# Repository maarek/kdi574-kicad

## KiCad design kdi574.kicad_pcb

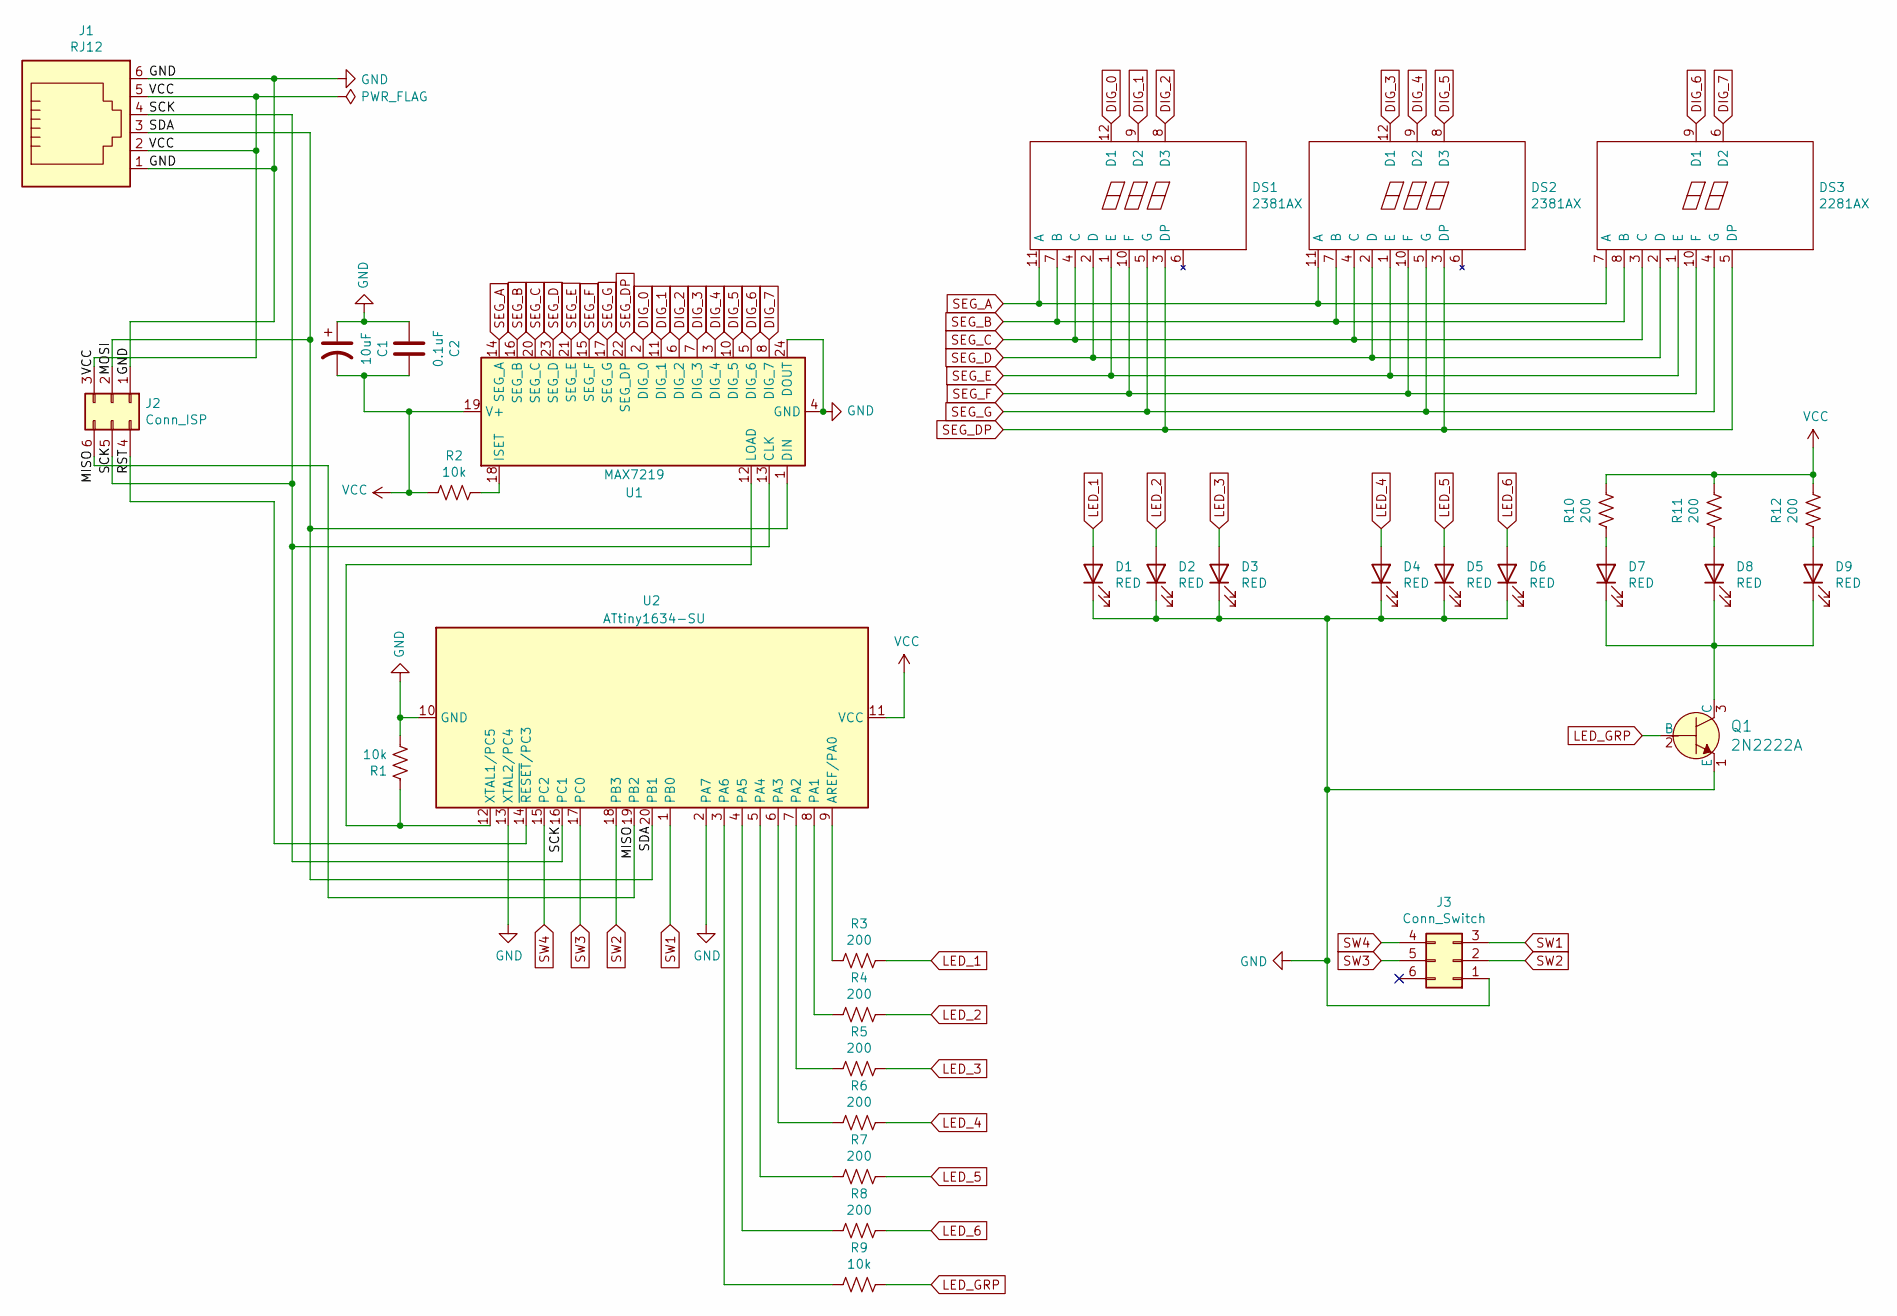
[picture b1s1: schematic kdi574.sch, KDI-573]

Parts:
C1: 10uF; C_1206_3216Metric
C2: 0.1uF; C_1206_3216Metric
D1, D2, D3, D4, D5, D6, D7, D8, D9: RED; LED_0603_1608Metric
DS1, DS2: 2381AX; 2381AS-DIP
DS3: 2281AX; 2281AS
J1: RJ12; RJ12_Amphenol_54601
J2: Conn_ISP; PinSocket_2x03_P2.54mm_Vertical
J3: Conn_Switch; PinHeader_2x03_P2.54mm_Vertical
Q1: 2N2222A; Trans_SOT-223-4; MPN 2N2222A; Digi-Key_PN 2N2222ACS-ND
R1, R2, R9: 10k; R_1206_3216Metric
R3, R4, R5, R6, R7, R8, R10, R11, R12: 200; R_1206_3216Metric
U1: MAX7219; SOIC-24_W7.50mm
U2: ATtiny1634-SU; SOIC-20W_7.5x12.8mm_P1.27mm

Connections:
/MISO: J2.6, U2.19 (PB2)
/RST: J2.4, U2.14 (~RESET~/PC3)
/SCK: J1.4, J2.5, U1.13 (CLK), U2.16 (PC1)
/SDA: J1.3, J2.2, U1.1 (DIN), U2.20 (PB1)
DIG_0: DS1.12 (D1), U1.2 (DIG_0)
DIG_1: DS1.9 (D2), U1.11 (DIG_1)
DIG_2: DS1.8 (D3), U1.6 (DIG_2)
DIG_3: DS2.12 (D1), U1.7 (DIG_3)
DIG_4: DS2.9 (D2), U1.3 (DIG_4)
DIG_5: DS2.8 (D3), U1.10 (DIG_5)
DIG_6: DS3.9 (D1), U1.5 (DIG_6)
DIG_7: DS3.6 (D2), U1.8 (DIG_7)
GND: C1.1, C2.2, D1.1 (K), D2.1 (K), D3.1 (K), D4.1 (K), D5.1 (K), D6.1 (K), J1.1, J1.6, J2.1, J3.1, Q1.1 (E), R1.1, U1.4 (GND), U1.9 (GND), U1.24 (DOUT), U2.2 (PA7), U2.10 (GND), U2.13 (XTAL2/PC4)
LED_1: D1.2 (A), R3.1
LED_2: D2.2 (A), R4.1
LED_3: D3.2 (A), R5.1
LED_4: D4.2 (A), R6.1
LED_5: D5.2 (A), R7.1
LED_6: D6.2 (A), R8.1
LED_GRP: Q1.2 (B), R9.1
unnamed: D7.1 (K), D8.1 (K), D9.1 (K), Q1.3 (C)
unnamed: D7.2 (A), R10.2
unnamed: D8.2 (A), R11.2
unnamed: D9.2 (A), R12.2
unnamed: R1.2, U1.12 (LOAD), U2.12 (XTAL1/PC5)
unnamed: R2.1, U1.18 (ISET)
unnamed: R3.2, U2.9 (AREF/PA0)
unnamed: R4.2, U2.8 (PA1)
unnamed: R5.2, U2.7 (PA2)
unnamed: R6.2, U2.6 (PA3)
unnamed: R7.2, U2.5 (PA4)
unnamed: R8.2, U2.4 (PA5)
unnamed: R9.2, U2.3 (PA6)
SEG_A: DS1.11 (A), DS2.11 (A), DS3.7 (A), U1.14 (SEG_A)
SEG_B: DS1.7 (B), DS2.7 (B), DS3.8 (B), U1.16 (SEG_B)
SEG_C: DS1.4 (C), DS2.4 (C), DS3.3 (C), U1.20 (SEG_C)
SEG_D: DS1.2 (D), DS2.2 (D), DS3.2 (D), U1.23 (SEG_D)
SEG_DP: DS1.3 (DP), DS2.3 (DP), DS3.5 (DP), U1.22 (SEG_DP)
SEG_E: DS1.1 (E), DS2.1 (E), DS3.1 (E), U1.21 (SEG_E)
SEG_F: DS1.10 (F), DS2.10 (F), DS3.10 (F), U1.15 (SEG_F)
SEG_G: DS1.5 (G), DS2.5 (G), DS3.4 (G), U1.17 (SEG_G)
SW1: J3.3, U2.1 (PB0)
SW2: J3.2, U2.18 (PB3)
SW3: J3.5, U2.17 (PC0)
SW4: J3.4, U2.15 (PC2)
VCC: C1.2, C2.1, J1.2, J1.5, J2.3, R2.2, R10.1, R11.1, R12.1, U1.19 (V+), U2.11 (VCC)

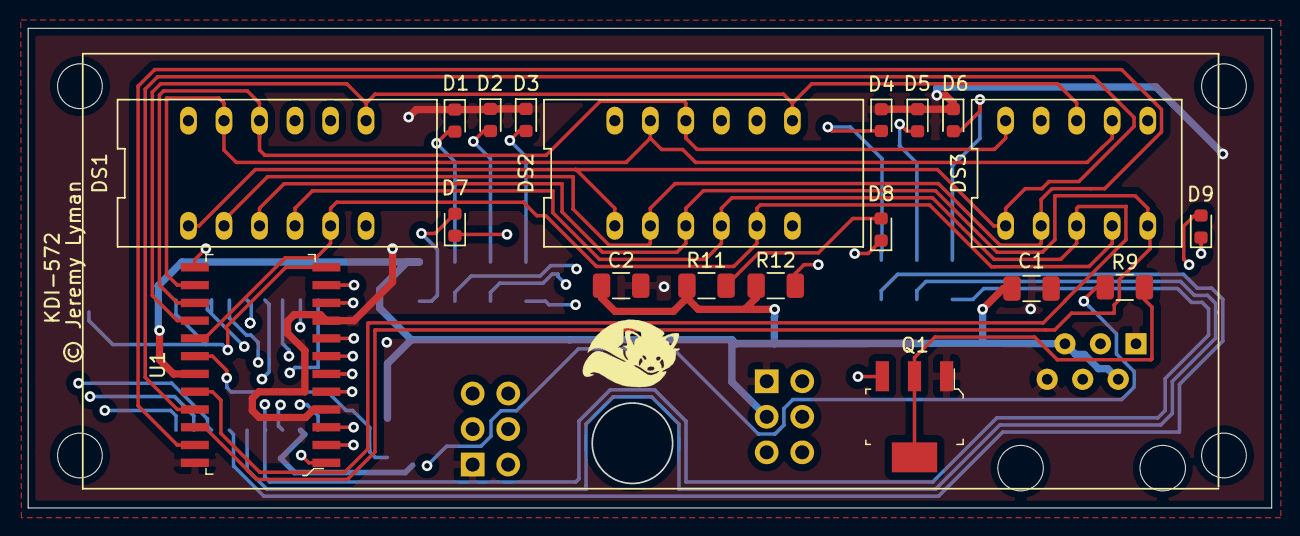
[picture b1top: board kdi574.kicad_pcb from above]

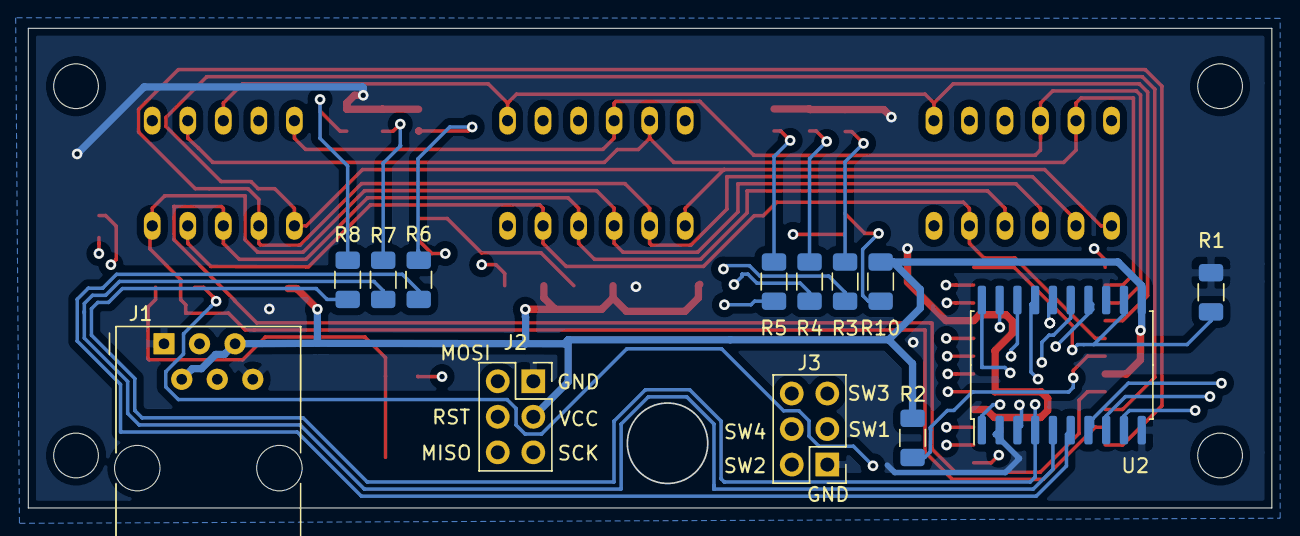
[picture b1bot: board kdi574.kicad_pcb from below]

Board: 4 copper layers, 88.8 x 34.2 mm, 32 parts (13 on the bottom side), 46 nets.

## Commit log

2020-05-24 Add kicad project

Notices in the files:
kdi574.kicad_pcb:
License: CC BY 4.0
© Jeremy Lyman
kdi574.sch:
creativecommons.org/licenses/by/4.0
